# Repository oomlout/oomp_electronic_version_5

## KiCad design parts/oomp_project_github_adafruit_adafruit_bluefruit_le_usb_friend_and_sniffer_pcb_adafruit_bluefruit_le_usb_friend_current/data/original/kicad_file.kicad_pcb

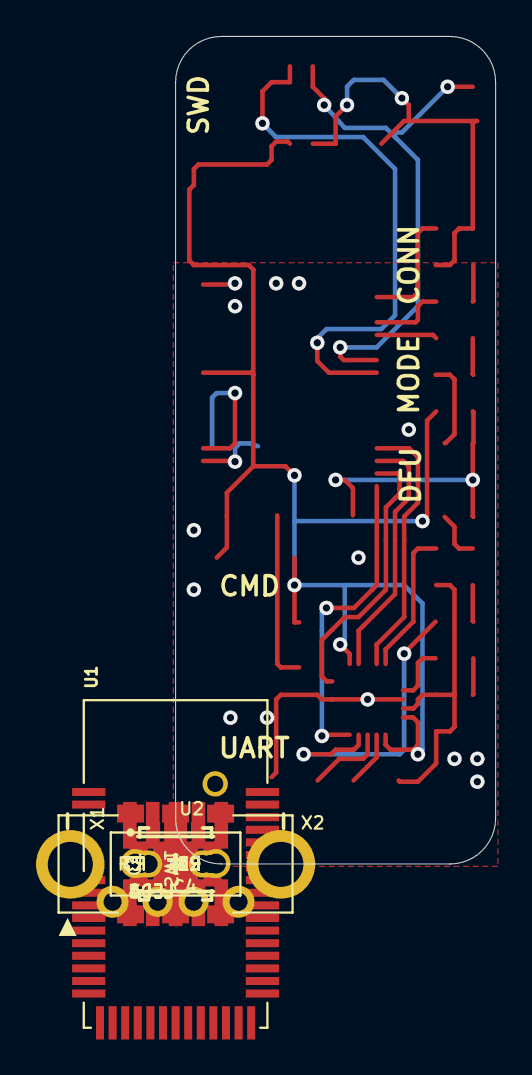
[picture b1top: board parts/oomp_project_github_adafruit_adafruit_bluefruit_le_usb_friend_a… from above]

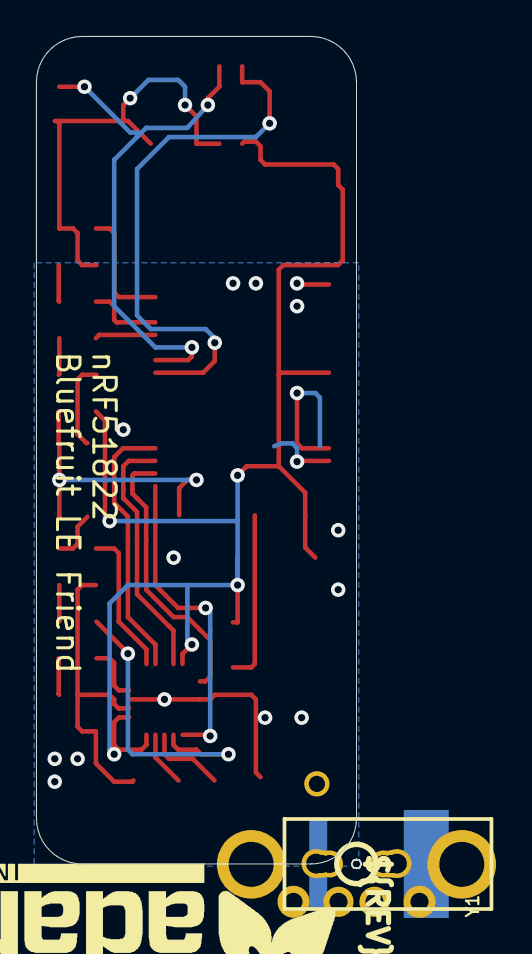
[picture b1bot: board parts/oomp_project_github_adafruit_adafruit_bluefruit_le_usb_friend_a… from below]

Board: 2 copper layers, 17.8 x 46.0 mm, 44 parts (3 on the bottom side), 25 nets.

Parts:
C1, C2: 1uF; _0805MP
C3, C4: 10uF; _0805MP
FID1, FID2: FIDUCIAL""; FIDUCIAL_1MM
LED1: YELLOW; CHIPLED_0805_NOOUTLINE
LED2: GREEN; CHIPLED_0805_NOOUTLINE
LED3: RED; CHIPLED_0805_NOOUTLINE
LED4: BLUE; CHIPLED_0805_NOOUTLINE
R1, R2, R3, R7: 1K; _0805MP
R4: 0; _0805MP
R5, R6: 10K; _0805MP
SW1: KMR2; BTN_KMR2_4.6X2.8
SW2: KMR2; EG1390
U1: nrf51822_32KB; BLE_MODULE_RAYTAC_MDBT40
U2: FT231XQ-x; QFN20_4MM
U$22: ADAFRUIT_TEXT_30MM
U$27: PCBFEAT-REV-056
UNK_HOLE_0: dummyfp0
UNK_HOLE_1: dummyfp1
UNK_HOLE_2: dummyfp2
UNK_HOLE_3: dummyfp3
UNK_HOLE_4: dummyfp4
UNK_HOLE_5: dummyfp5
UNK_HOLE_6: dummyfp6
UNK_HOLE_7: dummyfp7
UNK_HOLE_8: dummyfp8
UNK_HOLE_9: dummyfp9
UNK_HOLE_10: dummyfp10
UNK_HOLE_11: dummyfp11
UNK_HOLE_12: dummyfp12
UNK_HOLE_13: dummyfp13
UNK_HOLE_14: dummyfp14
UNK_HOLE_15: dummyfp15
UNK_HOLE_16: dummyfp16
UNK_HOLE_17: dummyfp17
X1: USB A; USB_A-THM
X2: 20317; 2X05_1.27MM_BOX_POSTS
Y1: DNC; CRYSTAL_CYL_2X6MM_SMT

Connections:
3.3V: C1.1, C4.1, R6.1, SW2.O1, U1.3, U1.14, U2.P$10, U2.P$11, U2.P$20, X2.1
5.0V: C3.1, R1.1, R2.1, U2.P$12, X1.VBUS
BOOTLOADER: R6.2, SW1.A, SW1.A', U1.24
CTS: U1.28, U2.P$19
GND: C1.2, C2.2, C3.2, C4.2, LED3.C, LED4.C, R4.2, R5.2, SW1.B, SW1.B', SW2.S1, U1.1, U1.2, U1.13, U1.16, U1.25, U1.42, U2.P$3, U2.P$13, U2.P$21, X1.GND, X2.3, X2.5, X2.9
MODE: SW2.P1, U1.18
unnamed: LED2.A, R2.2
unnamed: C2.1, U1.41
unnamed: LED3.A, R3.1
unnamed: LED1.A, R1.2
unnamed: LED1.C, U2.P$7
unnamed: LED2.C, U2.P$14
unnamed: R4.1, U2.P$16
unnamed: U2.P$8, X1.D+
unnamed: U2.P$9, X1.D-
unnamed: R3.2, U1.38
unnamed: R7.2, U1.39
unnamed: LED4.A, R7.1
unnamed: U1.9, Y1.2
unnamed: U1.10, Y1.1
RTS: U1.26, U2.P$6
RXD: U1.29, U2.P$17
SWCLK: R5.1, U1.36, X2.4
SWDIO: U1.35, X2.2
TXD: U1.27, U2.P$1

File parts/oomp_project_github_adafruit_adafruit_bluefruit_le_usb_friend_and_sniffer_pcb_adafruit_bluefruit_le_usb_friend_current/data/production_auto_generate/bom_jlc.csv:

Comment,Designator,Footprint,LCSC Part #
,U$22,Adafruit Bluefruit LE USB Friend-import-fps:ADAFRUIT_TEXT_30MM,
,U$27,Adafruit Bluefruit LE USB Friend-import-fps:PCBFEAT-REV-056,
0,R4,Adafruit Bluefruit LE USB Friend-import-fps:_0805MP,C2907288
10K,"R5,R6",Adafruit Bluefruit LE USB Friend-import-fps:_0805MP,C17414
10uF,"C3,C4",Adafruit Bluefruit LE USB Friend-import-fps:_0805MP,
1K,"R1,R2,R3,R7",Adafruit Bluefruit LE USB Friend-import-fps:_0805MP,C17513
1uF,"C1,C2",Adafruit Bluefruit LE USB Friend-import-fps:_0805MP,
20317,X2,Adafruit Bluefruit LE USB Friend-import-fps:2X05_1.27MM_BOX_POSTS,
BLUE,LED4,Adafruit Bluefruit LE USB Friend-import-fps:CHIPLED_0805_NOOUTLINE,
DNC,Y1,Adafruit Bluefruit LE USB Friend-import-fps:CRYSTAL_CYL_2X6MM_SMT,
FT231XQ-x ,U2,Adafruit Bluefruit LE USB Friend-import-fps:QFN20_4MM,
GREEN,LED2,Adafruit Bluefruit LE USB Friend-import-fps:CHIPLED_0805_NOOUTLINE,
KMR2,SW1,Adafruit Bluefruit LE USB Friend-import-fps:BTN_KMR2_4.6X2.8,
KMR2,SW2,Adafruit Bluefruit LE USB Friend-import-fps:EG1390,
nrf51822_32KB,U1,Adafruit Bluefruit LE USB Friend-import-fps:BLE_MODULE_RAYTAC_MDBT40,
RED,LED3,Adafruit Bluefruit LE USB Friend-import-fps:CHIPLED_0805_NOOUTLINE,
USB A,X1,Adafruit Bluefruit LE USB Friend-import-fps:USB_A-THM,
YELLOW,LED1,Adafruit Bluefruit LE USB Friend-import-fps:CHIPLED_0805_NOOUTLINE,

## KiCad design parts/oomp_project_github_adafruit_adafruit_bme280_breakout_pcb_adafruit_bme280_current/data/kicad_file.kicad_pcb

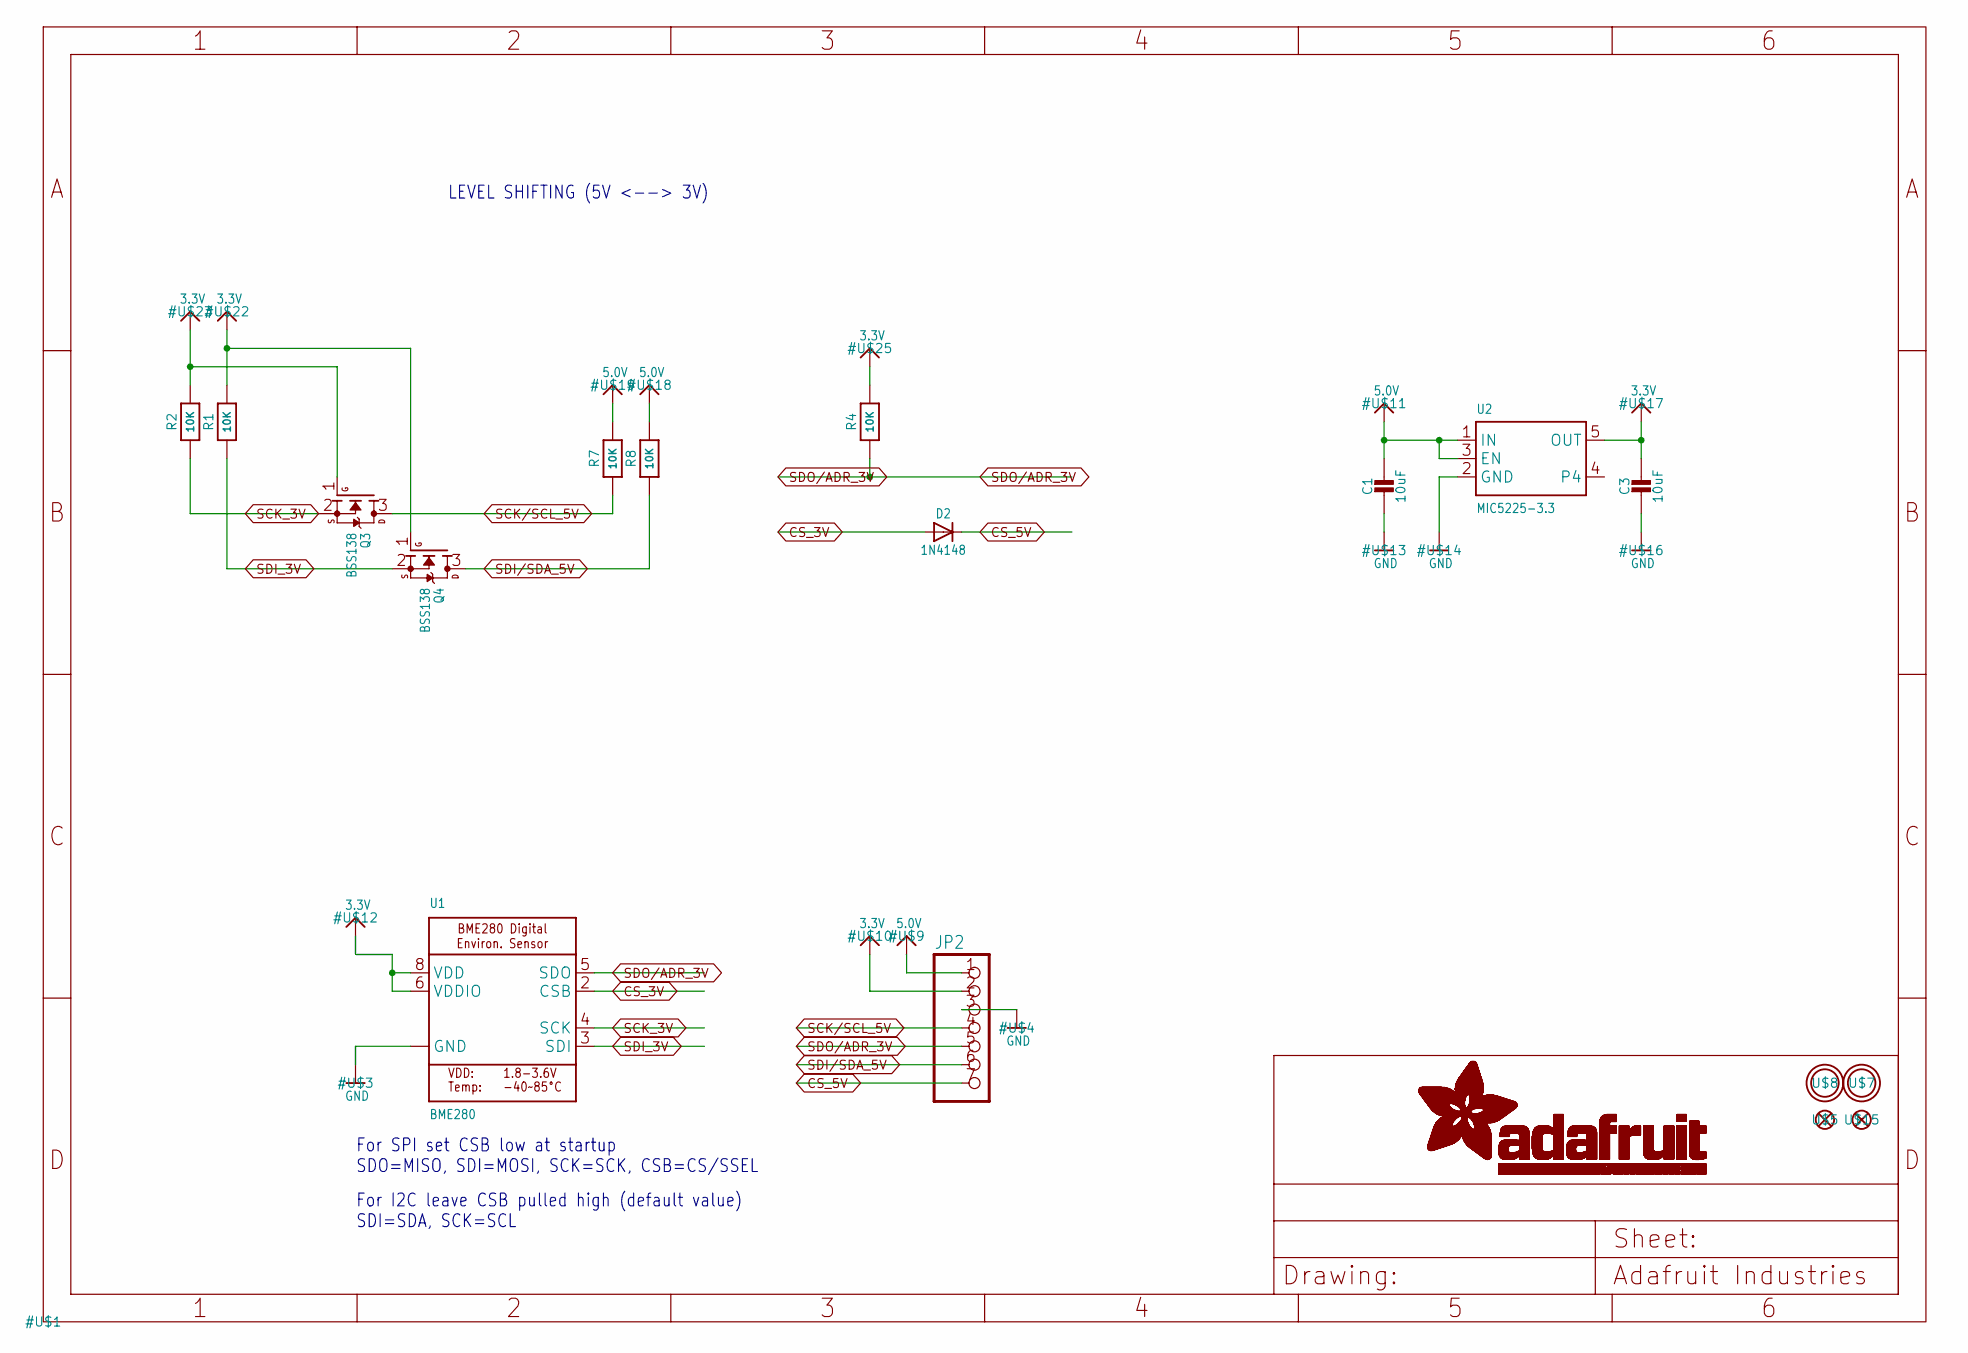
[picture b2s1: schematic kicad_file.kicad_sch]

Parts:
C1, C3: 10uF; 0805-NO
D2: 1N4148; SOD-323
JP2: HEADER-1X770MIL; 1X07_ROUND_70
Q3, Q4: BSS138; SOT23-WIDE
R1, R2, R7, R8: 10K; 0805-NO
R4: 10K; _0805MP
U1: BME280
U2: MIC5225-3.3; SOT23-5
U$5, U$15: FIDUCIAL""; FIDUCIAL_1MM
U$7, U$8: MOUNTINGHOLE2.0; MOUNTINGHOLE_2.0_PLATED

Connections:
3.3V: C3.1, JP2.2, Q3.1 (G), Q4.1 (G), R1.2, R2.2, R4.2, U1.6 (VDDIO), U1.8 (VDD), U2.5 (OUT)
5.0V: C1.1, JP2.1, R7.2, R8.2, U2.1 (IN), U2.3 (EN)
CS_3V: D2.A, U1.2 (CSB)
CS_5V: D2.C, JP2.7
GND: C1.2, C3.2, JP2.3, U1.1 (GND), U1.7 (GND), U2.2 (GND)
SCK/SCL_5V: JP2.4, Q3.3 (D), R7.1
SCK_3V: Q3.2 (S), R2.1, U1.4 (SCK)
SDI/SDA_5V: JP2.6, Q4.3 (D), R8.1
SDI_3V: Q4.2 (S), R1.1, U1.3 (SDI)
SDO/ADR_3V: JP2.5, R4.1, U1.5 (SDO)

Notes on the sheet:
For I2C leave CSB pulled high (default value) SDI=SDA, SCK=SCL
For SPI set CSB low at startup SDO=MISO, SDI=MOSI, SCK=SCK, CSB=CS/SSEL
LEVEL SHIFTING (5V <--> 3V)

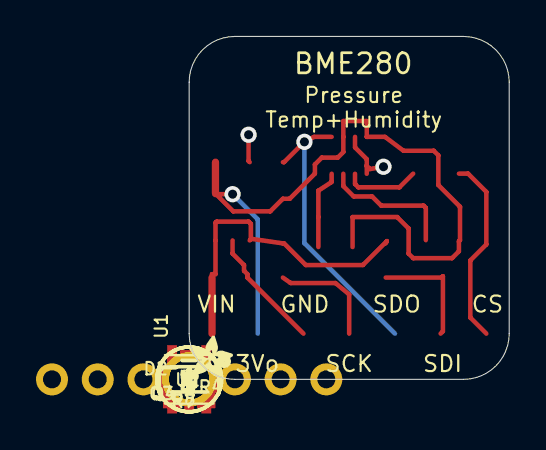
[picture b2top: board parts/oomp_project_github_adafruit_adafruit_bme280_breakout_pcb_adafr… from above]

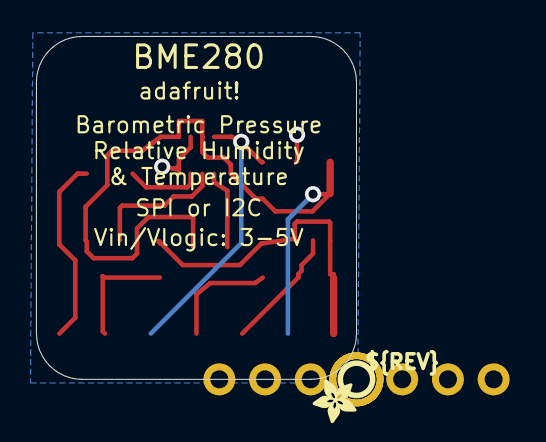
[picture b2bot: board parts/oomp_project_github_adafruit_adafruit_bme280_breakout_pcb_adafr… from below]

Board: 2 copper layers, 17.8 x 19.1 mm, 20 parts (2 on the bottom side), 10 nets.

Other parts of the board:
U$2, U$6: ADAFRUIT_2.5MM
U$20: PCBFEAT-REV-040

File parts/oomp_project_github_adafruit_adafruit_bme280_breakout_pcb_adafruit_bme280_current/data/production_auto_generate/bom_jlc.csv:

Comment,Designator,Footprint,LCSC Part #
,JP2,Adafruit BME280-import-fps:1X07_ROUND_70,C7501585
,"U$2,U$6",Adafruit BME280-import-fps:ADAFRUIT_2.5MM,
,U$20,Adafruit BME280-import-fps:PCBFEAT-REV-040,
10K,"R1,R2,R7,R8",Adafruit BME280-import-fps:0805-NO,C17414
10K,R4,Adafruit BME280-import-fps:_0805MP,C17414
10uF,"C1,C3",Adafruit BME280-import-fps:0805-NO,
1N4148,D2,Adafruit BME280-import-fps:SOD-323,
BME280,U1,Adafruit BME280-import-fps:BME280,
BSS138,"Q3,Q4",Adafruit BME280-import-fps:SOT23-WIDE,C52895
"FIDUCIAL""""","U$5,U$15",Adafruit BME280-import-fps:FIDUCIAL_1MM,
MIC5225-3.3,U2,Adafruit BME280-import-fps:SOT23-5,

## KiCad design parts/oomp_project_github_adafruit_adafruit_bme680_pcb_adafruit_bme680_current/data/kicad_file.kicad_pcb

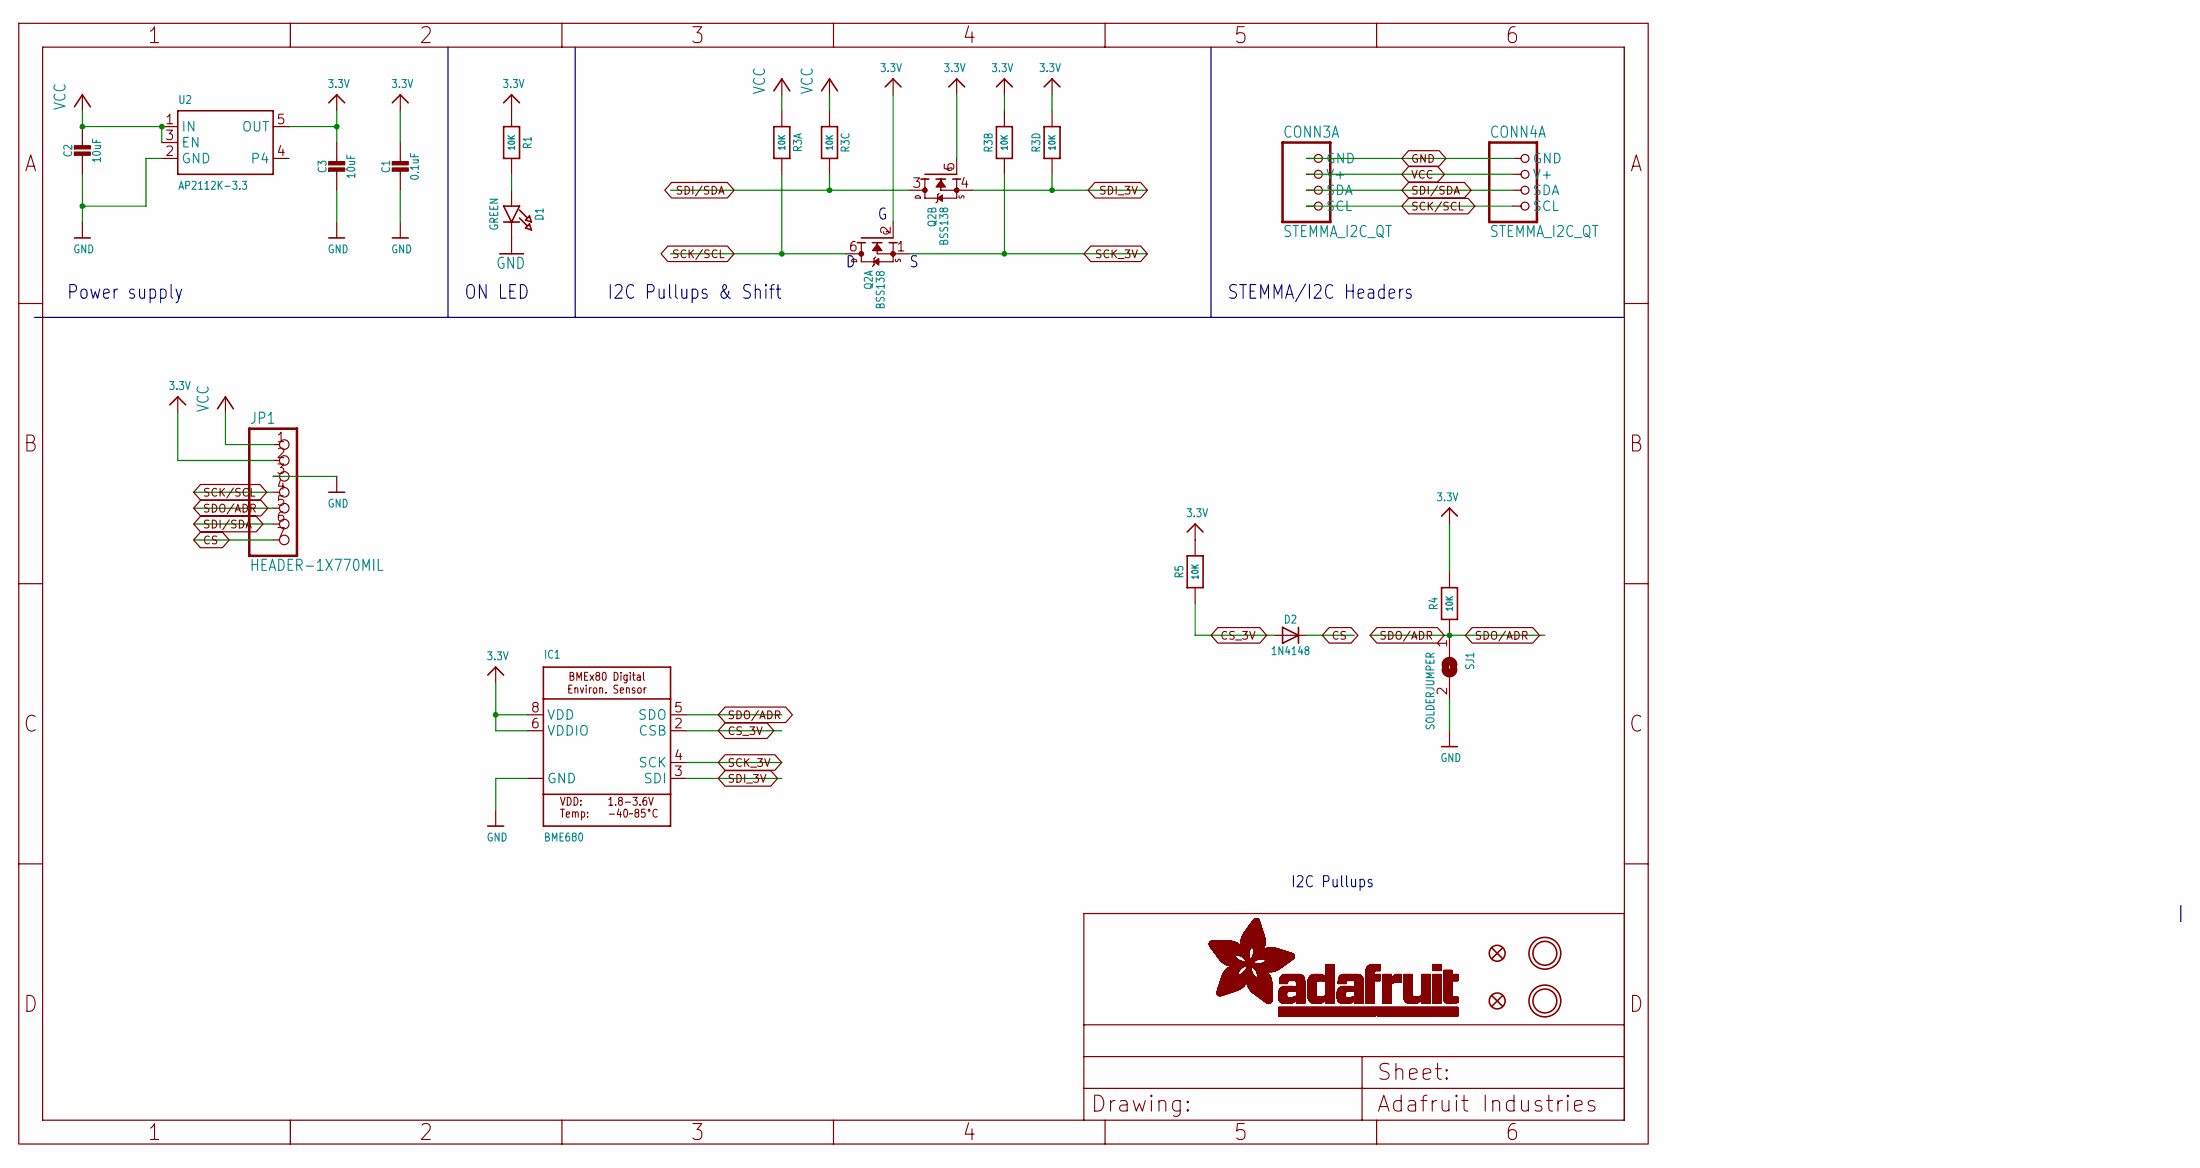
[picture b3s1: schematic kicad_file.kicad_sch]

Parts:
C1: 0.1uF; 0603-NO
C2, C3: 10uF; 0805-NO
CONN3, CONN4: STEMMA_I2C_QT; JST_SH4
D1: GREEN; CHIPLED_0603_NOOUTLINE
D2: 1N4148; SOD-323
FID3, FID4: FIDUCIAL_1MM
IC1: BME680
JP1: HEADER-1X770MIL; 1X07_ROUND_70
Q2: BSS138; SOT363
R1, R4, R5: 10K; 0603-NO
R3: 10K; RESPACK_4X0603
SJ1: SOLDERJUMPER; SOLDERJUMPER_ARROW_NOPASTE
U2: AP2112K-3.3; SOT23-5
U$1, U$17: MOUNTINGHOLE2.5; MOUNTINGHOLE_2.5_PLATED

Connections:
3.3V: C1.1, C3.1, IC1.6 (VDDIO), IC1.8 (VDD), JP1.2, Q2.2 (G), Q2.5 (G), R1.1, R3.2 (1), R3.4 (1), R4.2, R5.2, U2.5 (OUT)
CS: D2.C, JP1.7
CS_3V: D2.A, IC1.2 (CSB), R5.1
GND: C1.2, C2.2, C3.2, CONN3.1 (GND), CONN4.1 (GND), D1.C, IC1.1 (GND), IC1.7 (GND), JP1.3, SJ1.2, U2.2 (GND)
unnamed: D1.A, R1.2
SCK/SCL: CONN3.4 (SCL), CONN4.4 (SCL), JP1.4, Q2.6 (D), R3.8 (2)
SCK_3V: IC1.4 (SCK), Q2.1 (S), R3.7 (2)
SDI/SDA: CONN3.3 (SDA), CONN4.3 (SDA), JP1.6, Q2.3 (D), R3.6 (2)
SDI_3V: IC1.3 (SDI), Q2.4 (S), R3.5 (2)
SDO/ADR: IC1.5 (SDO), JP1.5, R4.1, SJ1.1
VCC: C2.1, CONN3.2 (V+), CONN4.2 (V+), JP1.1, R3.1, R3.3 (1), U2.1 (IN), U2.3 (EN)

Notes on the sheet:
Power supply
ON LED
I2C Pullups
STEMMA/I2C Headers
I2C Pullups & Shift

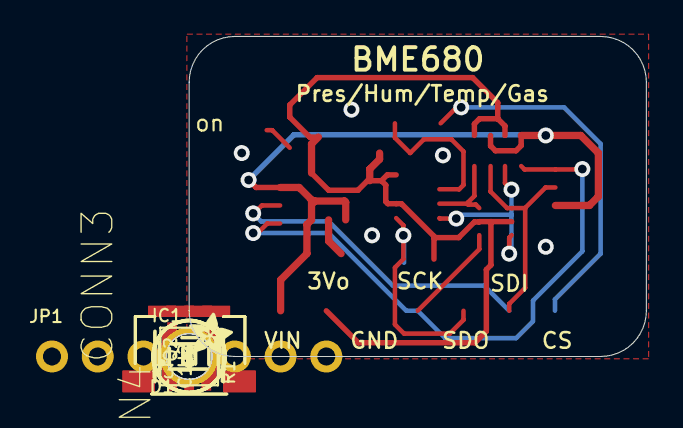
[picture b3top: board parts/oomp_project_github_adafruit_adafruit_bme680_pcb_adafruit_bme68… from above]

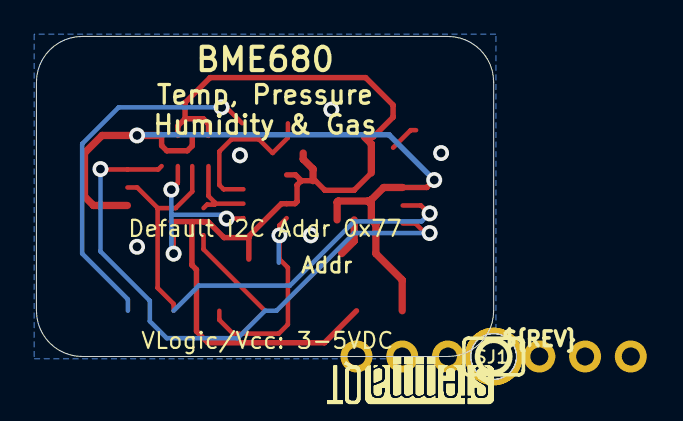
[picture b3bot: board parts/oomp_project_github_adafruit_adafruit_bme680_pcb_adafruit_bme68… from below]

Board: 2 copper layers, 25.4 x 17.8 mm, 26 parts (4 on the bottom side), 11 nets.

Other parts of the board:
U$4: ADAFRUIT_2.5MM
U$25: PCBFEAT-REV-040
U$30, U$31: STEMMAQT
UNK_HOLE_0: dummyfp0
UNK_HOLE_1: dummyfp1

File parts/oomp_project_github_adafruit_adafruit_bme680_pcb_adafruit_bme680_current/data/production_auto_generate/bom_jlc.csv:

Comment,Designator,Footprint,LCSC Part #
,JP1,Adafruit BME680-import-fps:1X07_ROUND_70,C7501585
,U$4,Adafruit BME680-import-fps:ADAFRUIT_2.5MM,
,U$25,Adafruit BME680-import-fps:PCBFEAT-REV-040,
,"U$30,U$31",Adafruit BME680-import-fps:STEMMAQT,
0.1uF,C1,Adafruit BME680-import-fps:0603-NO,C14663
10K,"R1,R4,R5",Adafruit BME680-import-fps:0603-NO,C98220
10K,R3,Adafruit BME680-import-fps:RESPACK_4X0603,C98220
10uF,"C2,C3",Adafruit BME680-import-fps:0805-NO,
1N4148,D2,Adafruit BME680-import-fps:SOD-323,
AP2112K-3.3,U2,Adafruit BME680-import-fps:SOT23-5,
BME680,IC1,Adafruit BME680-import-fps:BME680,
BSS138,Q2,Adafruit BME680-import-fps:SOT363,
GREEN,D1,Adafruit BME680-import-fps:CHIPLED_0603_NOOUTLINE,
STEMMA_I2C_QT,"CONN3,CONN4",Adafruit BME680-import-fps:JST_SH4,C160404

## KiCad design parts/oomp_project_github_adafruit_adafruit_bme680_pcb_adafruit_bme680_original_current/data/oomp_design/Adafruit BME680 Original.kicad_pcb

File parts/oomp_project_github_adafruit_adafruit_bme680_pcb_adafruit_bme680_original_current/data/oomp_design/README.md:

# OOMP KiCad design copy

Open `Adafruit BME680 Original.kicad_pro` (or the `.kicad_pcb` / `.kicad_sch`) in KiCad. Local OOMP libraries are under `libraries/`. Original inputs are preserved in [../original/](../original/).

Only verified unchanged installed KiCad defaults were renamed. Modified, custom, unmatched and unavailable items remain unchanged. Soldering variants are never swapped during conversion. Existing pad coordinates, nets and UUIDs are preserved.

See [conversion_report.yaml](conversion_report.yaml) for every conversion and skip. Copy this directory before editing; regeneration refuses to overwrite edited design files.

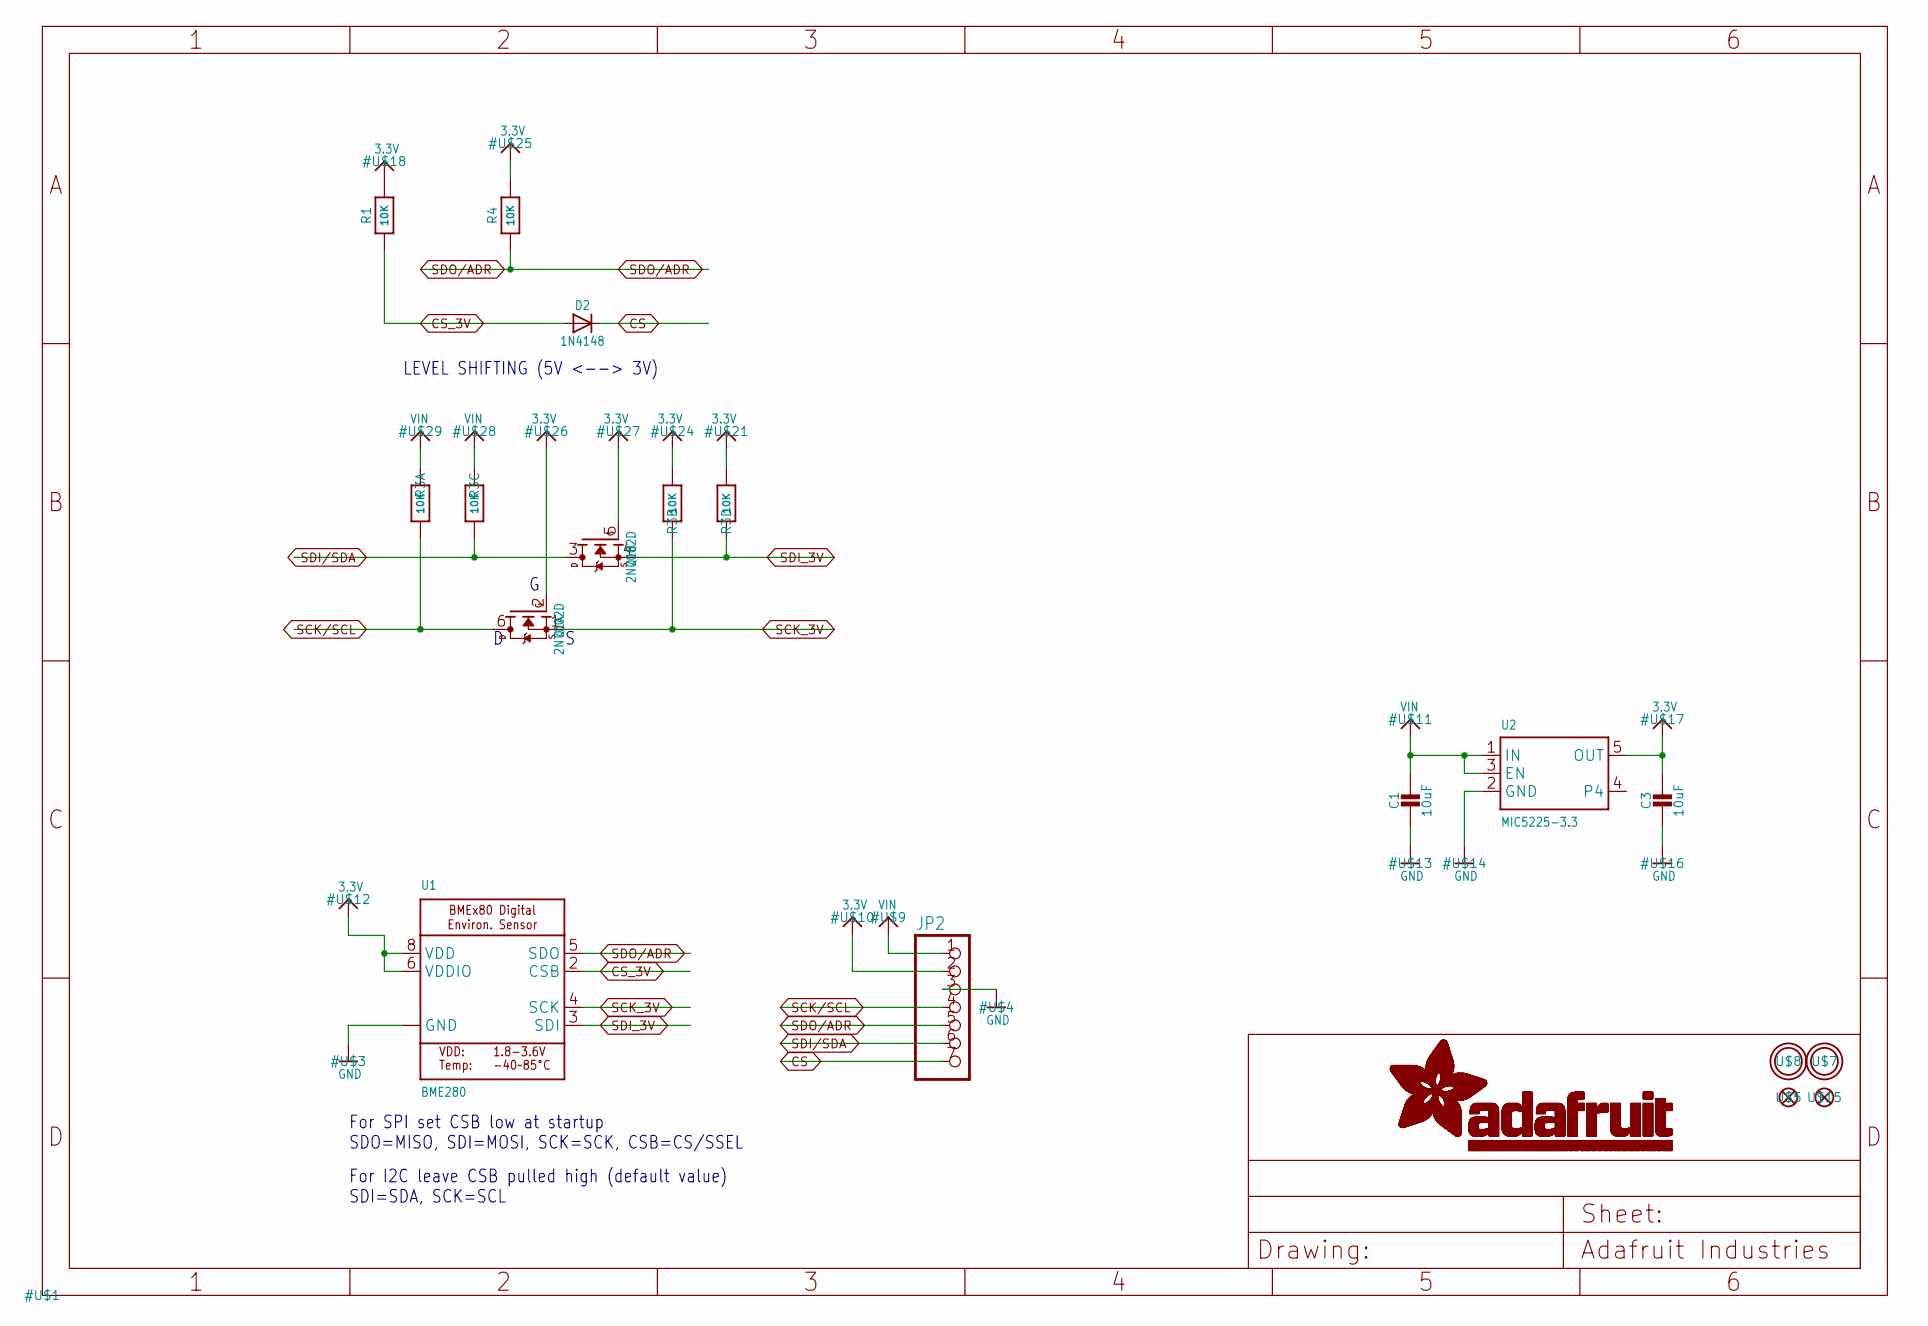
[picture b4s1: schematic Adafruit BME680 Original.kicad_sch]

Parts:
C1, C3: 10uF; 0805-NO
D2: 1N4148; SOD-323
JP2: HEADER-1X770MIL; 1X07_ROUND_70
Q1: 2N7002D; SOT363
R1, R4: 10K; 0603-NO
R3: 10K; RESPACK_4X0603
U1: BME280; BME680
U2: MIC5225-3.3; SOT23-5
U$5, U$15: FIDUCIAL_1MM
U$7, U$8: MOUNTINGHOLE2.0; MOUNTINGHOLE_2.0_PLATED

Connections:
3.3V: C3.1, JP2.2, Q1.2 (G), Q1.5 (G), R1.2, R3.2 (1), R3.4 (1), R4.2, U1.6 (VDDIO), U1.8 (VDD), U2.5 (OUT)
CS: D2.C, JP2.7
CS_3V: D2.A, R1.1, U1.2 (CSB)
GND: C1.2, C3.2, JP2.3, U1.1 (GND), U1.7 (GND), U2.2 (GND)
SCK/SCL: JP2.4, Q1.6 (D), R3.8 (2)
SCK_3V: Q1.1 (S), R3.7 (2), U1.4 (SCK)
SDI/SDA: JP2.6, Q1.3 (D), R3.6 (2)
SDI_3V: Q1.4 (S), R3.5 (2), U1.3 (SDI)
SDO/ADR: JP2.5, R4.1, U1.5 (SDO)
VIN: C1.1, JP2.1, R3.1, R3.3 (1), U2.1 (IN), U2.3 (EN)

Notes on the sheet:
LEVEL SHIFTING (5V <--> 3V)
For SPI set CSB low at startup SDO=MISO, SDI=MOSI, SCK=SCK, CSB=CS/SSEL
For I2C leave CSB pulled high (default value) SDI=SDA, SCK=SCL

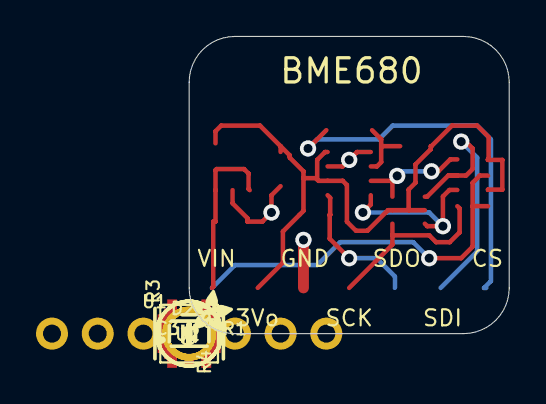
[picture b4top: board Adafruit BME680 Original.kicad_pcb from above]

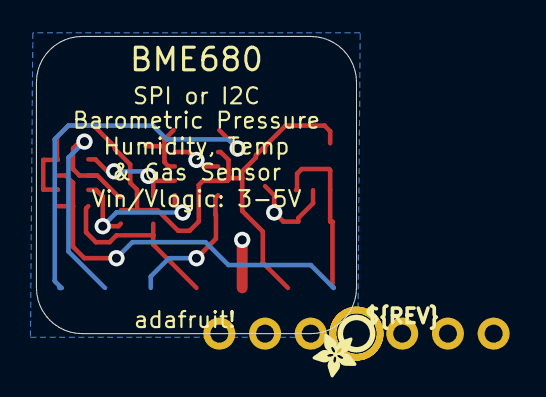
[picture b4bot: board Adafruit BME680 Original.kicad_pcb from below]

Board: 2 copper layers, 17.8 x 16.5 mm, 17 parts (2 on the bottom side), 10 nets.

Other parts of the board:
U$2, U$6: ADAFRUIT_2.5MM
U$20: PCBFEAT-REV-040

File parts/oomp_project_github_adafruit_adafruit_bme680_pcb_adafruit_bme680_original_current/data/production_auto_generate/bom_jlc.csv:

Comment,Designator,Footprint,LCSC Part #
,JP2,Adafruit BME680 Original-import-fps:1X07_ROUND_70,C7501585
,"U$2,U$6",Adafruit BME680 Original-import-fps:ADAFRUIT_2.5MM,
,U$20,Adafruit BME680 Original-import-fps:PCBFEAT-REV-040,
10K,"R1,R4",Adafruit BME680 Original-import-fps:0603-NO,C98220
10K,R3,Adafruit BME680 Original-import-fps:RESPACK_4X0603,C98220
10uF,"C1,C3",Adafruit BME680 Original-import-fps:0805-NO,
1N4148,D2,Adafruit BME680 Original-import-fps:SOD-323,
2N7002D,Q1,Adafruit BME680 Original-import-fps:SOT363,
BME280,U1,Adafruit BME680 Original-import-fps:BME680,
FIDUCIAL_1MM,"U$5,U$15",Adafruit BME680 Original-import-fps:FIDUCIAL_1MM,
MIC5225-3.3,U2,Adafruit BME680 Original-import-fps:SOT23-5,

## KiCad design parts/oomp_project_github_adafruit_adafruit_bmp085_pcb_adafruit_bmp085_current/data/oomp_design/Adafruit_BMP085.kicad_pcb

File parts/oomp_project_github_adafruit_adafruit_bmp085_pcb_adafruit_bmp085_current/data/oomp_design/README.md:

# OOMP KiCad design copy

Open `Adafruit_BMP085.kicad_pro` (or the `.kicad_pcb` / `.kicad_sch`) in KiCad. Local OOMP libraries are under `libraries/`. Original inputs are preserved in [../original/](../original/).

Only verified unchanged installed KiCad defaults were renamed. Modified, custom, unmatched and unavailable items remain unchanged. Soldering variants are never swapped during conversion. Existing pad coordinates, nets and UUIDs are preserved.

See [conversion_report.yaml](conversion_report.yaml) for every conversion and skip. Copy this directory before editing; regeneration refuses to overwrite edited design files.

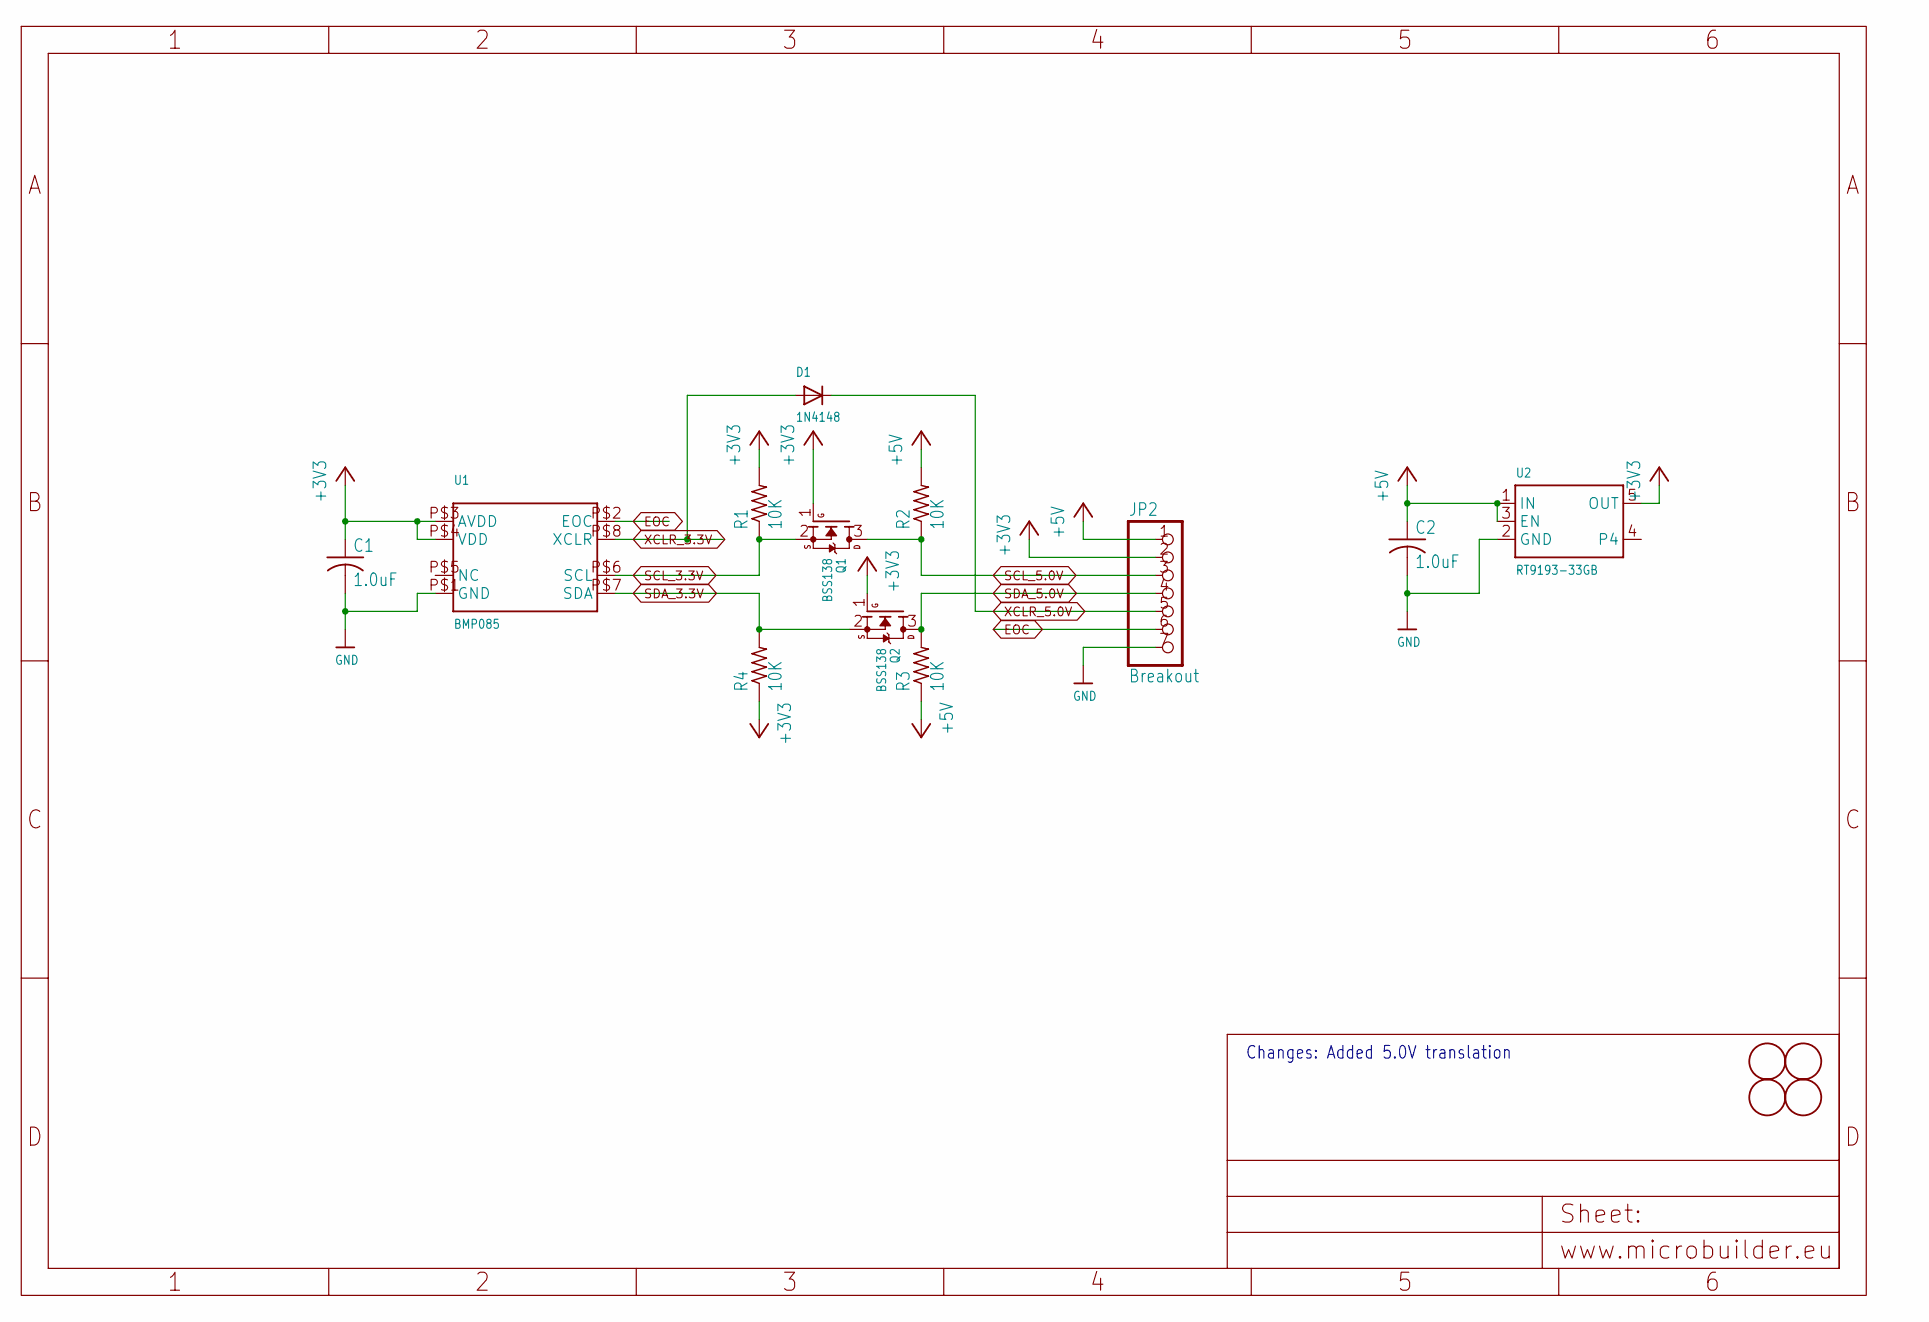
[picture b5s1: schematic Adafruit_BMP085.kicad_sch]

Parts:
C1, C2: 1.0uF; C0805
D1: 1N4148; SOD-323F
JP2: Breakout; 1X07_ROUND_76
Q1, Q2: BSS138; SOT23
R1, R2, R3, R4: 10K; R0805
U1: BMP085
U2: RT9193-33GB; SOT23-5
U$1, U$15: FIDUCIAL; FIDUCIAL_1MM
U$7, U$8: MOUNTINGHOLE2.0; MOUNTINGHOLE_2.0_PLATED

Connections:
+3V3: C1.1, JP2.2, Q1.1 (G), Q2.1 (G), R1.2, R4.1, U1.P$3 (AVDD), U1.P$4 (VDD), U2.5 (OUT)
+5V: C2.1, JP2.1, R2.2, R3.1, U2.1 (IN), U2.3 (EN)
EOC: JP2.6, U1.P$2 (EOC)
GND: C1.2, C2.2, JP2.7, U1.P$1 (GND), U2.2 (GND)
SCL_3.3V: Q1.2 (S), R1.1, U1.P$6 (SCL)
SCL_5.0V: JP2.3, Q1.3 (D), R2.1
SDA_3.3V: Q2.2 (S), R4.2, U1.P$7 (SDA)
SDA_5.0V: JP2.4, Q2.3 (D), R3.2
XCLR_3.3V: D1.A, U1.P$8 (XCLR)
XCLR_5.0V: D1.C, JP2.5

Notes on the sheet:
Changes: Added 5.0V translation

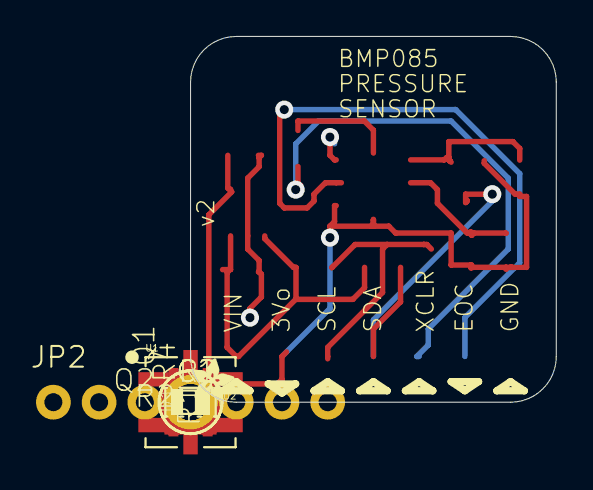
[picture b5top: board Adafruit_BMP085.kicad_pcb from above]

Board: 2 copper layers, 20.3 x 20.3 mm, 18 parts (1 on the bottom side), 10 nets.

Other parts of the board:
U$2, U$6: ADAFRUIT_2.5MM

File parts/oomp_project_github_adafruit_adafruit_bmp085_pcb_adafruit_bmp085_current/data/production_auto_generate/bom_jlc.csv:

Comment,Designator,Footprint,LCSC Part #
,"U$2,U$6",Adafruit_BMP085-import-fps:ADAFRUIT_2.5MM,
1.0uF,"C1,C2",Adafruit_BMP085-import-fps:C0805,
10K,"R1,R2,R3,R4",Adafruit_BMP085-import-fps:R0805,C17414
1N4148,D1,Adafruit_BMP085-import-fps:SOD-323F,
BMP085,U1,Adafruit_BMP085-import-fps:BMP085,
Breakout,JP2,Adafruit_BMP085-import-fps:1X07_ROUND_76,C7501585
BSS138,"Q1,Q2",Adafruit_BMP085-import-fps:SOT23,C52895
FIDUCIAL,"U$1,U$15",Adafruit_BMP085-import-fps:FIDUCIAL_1MM,
RT9193-33GB,U2,Adafruit_BMP085-import-fps:SOT23-5,
